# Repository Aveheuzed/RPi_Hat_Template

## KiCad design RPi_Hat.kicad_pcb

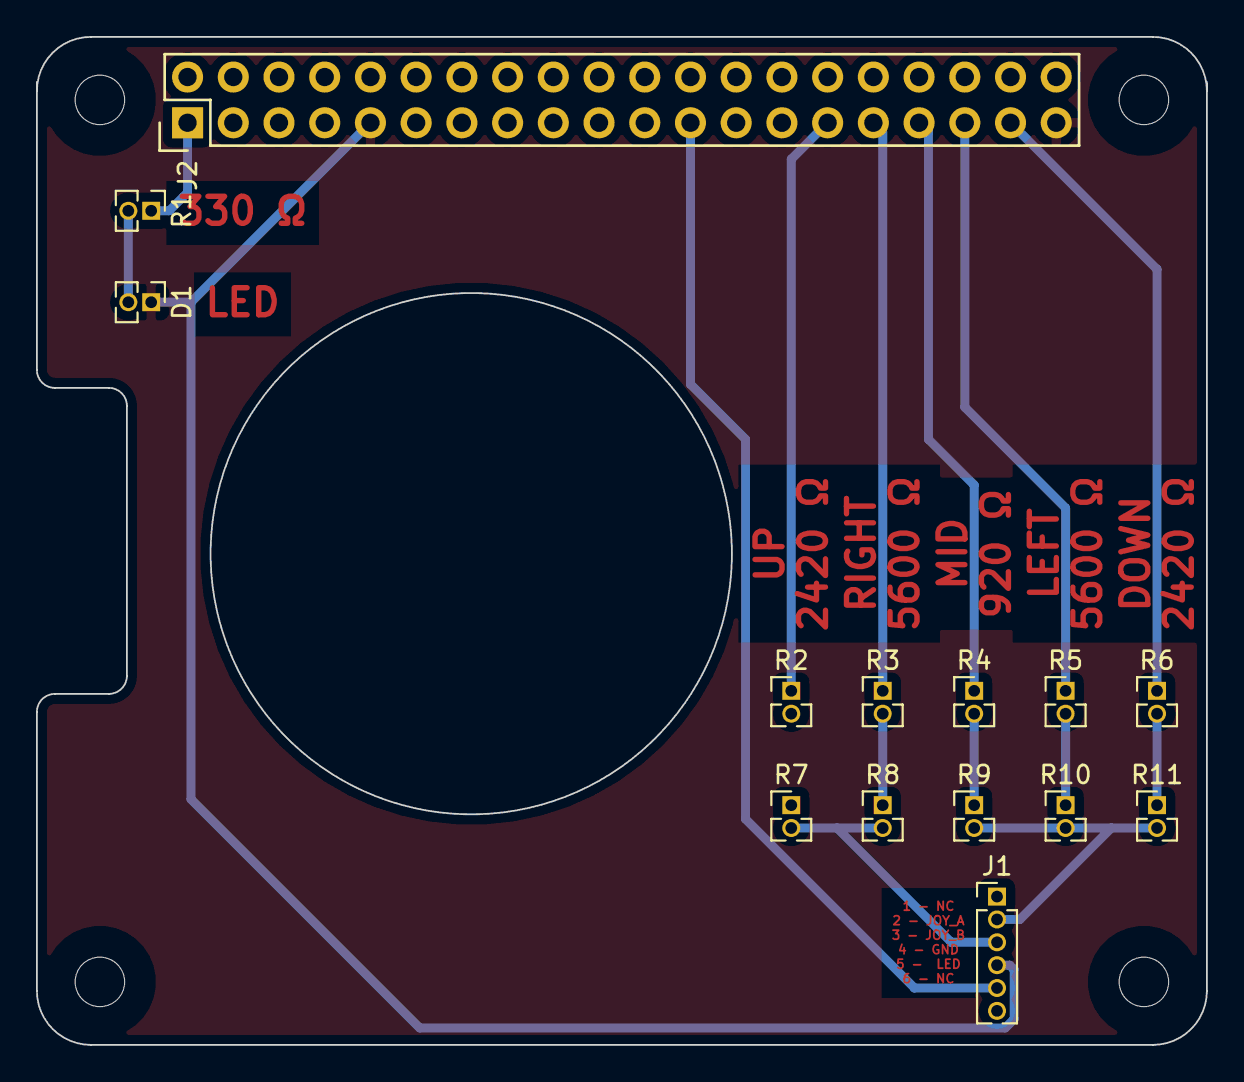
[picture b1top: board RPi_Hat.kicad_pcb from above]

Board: 2 copper layers, 65.0 x 56.0 mm, 14 parts (0 on the bottom side), 16 nets.

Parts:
D1: LED; PinHeader_1x02_P1.27mm_Vertical
J1: Conn_01x06; PinHeader_1x06_P1.27mm_Vertical
J2: RPi_GPIO; Pin_Header_Straight_2x20
R1: 330; PinHeader_1x02_P1.27mm_Vertical
R2, R6: 2420; PinHeader_1x02_P1.27mm_Vertical
R3, R5: 5600; PinHeader_1x02_P1.27mm_Vertical
R4: 920; PinHeader_1x02_P1.27mm_Vertical
R7, R8, R9, R10, R11: 0; PinHeader_1x02_P1.27mm_Vertical

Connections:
DOWN: J1.2, R9.2, R10.2, R11.2
GND: D1.1, J1.4, J2.9, J2.39
LED: J1.5, J2.23
unnamed: D1.2, R1.2
unnamed: J2.1, R1.1
unnamed: J2.29, R2.1
unnamed: J2.31, R3.1
unnamed: J2.33, R4.1
unnamed: J2.35, R5.1
unnamed: J2.37, R6.1
unnamed: R2.2, R7.1
unnamed: R3.2, R8.1
unnamed: R4.2, R9.1
unnamed: R5.2, R10.1
unnamed: R6.2, R11.1
RIGHT: J1.3, R7.2, R8.2

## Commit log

2021-06-30 schematics updated to adapt tou our project
2021-07-02 final prototype
